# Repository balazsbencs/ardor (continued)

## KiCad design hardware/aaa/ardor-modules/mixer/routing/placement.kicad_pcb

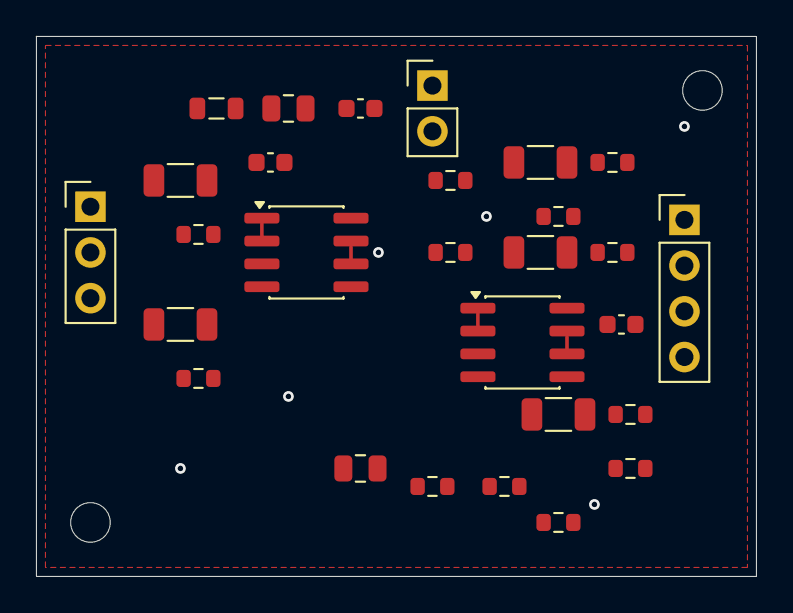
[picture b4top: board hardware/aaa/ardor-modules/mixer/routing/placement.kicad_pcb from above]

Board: 2 copper layers, 40.0 x 30.0 mm, 30 parts (0 on the bottom side), 19 nets.

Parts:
C101: 22u / 25V X5R; C_0805_2012Metric
C102, C404, C405: 100n / 50V X7R; C_0603_1608Metric
C401, C402, C407, C408, C409: 10u / 50V X5R; C_1206_3216Metric
C403: 10u / 25V X5R; C_0805_2012Metric
FB101: BLM21PG601SN1D; L_0805_2012Metric
H1, H2: MountingHole_2.2mm_M2
J101: +5V / GND; PinHeader_1x02_P2.54mm_Vertical
J102: AUDIO_L / GND / AUDIO_R; PinHeader_1x03_P2.54mm_Vertical
J103: OUT_L / GND / OUT_R / OUT_MONO; PinHeader_1x04_P2.54mm_Vertical
R401, R402, R410, R411, R412: 100kR / 1%; R_0603_1608Metric
R403, R404, R405, R406: 10kR / 1%; R_0603_1608Metric
R407, R408, R409: 100R / 1%; R_0603_1608Metric
U401, U402: TLV9002IDR; SOIC-8_3.9x4.9mm_P1.27mm

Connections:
/+5V: FB101.1, J101.1
/+5V_A: C101.1, C102.1, C404.1, C405.1, FB101.2, R405.1, U401.8, U402.8
/GND: C101.2, C102.2, C403.2, C404.2, C405.2, J101.2, J102.2, J103.2, R406.2, R410.2, R411.2, R412.2, U401.4, U402.4
/VREF: R401.2, R402.2, U402.6, U402.7
unnamed: C407.2, R407.1, R410.1
unnamed: C408.2, R408.1, R411.1
unnamed: C409.2, R409.1, R412.1
unnamed: C401.1, J102.1
unnamed: C402.1, J102.3
unnamed: J103.1, R407.2
unnamed: J103.3, R408.2
unnamed: J103.4, R409.2
unnamed: C401.2, R401.1, U401.3
unnamed: C407.1, R403.1, U401.1, U401.2
unnamed: C402.2, R402.1, U401.5
unnamed: C408.1, R404.1, U401.6, U401.7
unnamed: R403.2, R404.2, U402.3
unnamed: C409.1, U402.1, U402.2
unnamed: C403.1, R405.2, R406.1, U402.5

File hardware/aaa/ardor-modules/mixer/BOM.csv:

Reference,Value,Footprint,MPN,JLCPCB Part #,Assembly
J102,STEREO AUDIO INPUT FROM SOURCE,Connector_PinHeader_2.54mm:PinHeader_1x03_P2.54mm_Vertical,PinHeader_1x03_P2.54mm_Vertical,,Manual
J101,5V POWER INPUT,Connector_PinHeader_2.54mm:PinHeader_1x02_P2.54mm_Vertical,PinHeader_1x02_P2.54mm_Vertical,,Manual
J103,"BUFFERED STEREO + MONO AUDIO
OUTPUT",Connector_PinHeader_2.54mm:PinHeader_1x04_P2.54mm_Vertical,PinHeader_1x04_P2.54mm_Vertical,,Manual
FB101,600R@100MHz,Inductor_SMD:L_0805_2012Metric,Murata BLM21PG601SN1D,C41556732,SMT
C101,22u / 25V X5R,Capacitor_SMD:C_0805_2012Metric,Samsung Electro-Mechanics CL21A226MAQNNNE,C45783,SMT
C102,100n / 50V X7R,Capacitor_SMD:C_0603_1608Metric,YAGEO CC0603KRX7R9BB104,C14663,SMT
C401,10u / 50V X5R,Capacitor_SMD:C_1206_3216Metric,Samsung Electro-Mechanics CL31A106KBHNNNE,C13585,SMT
R401,100k / 1%,Resistor_SMD:R_0603_1608Metric,UNI-ROYAL 0603WAF1003T5E,C25803,SMT
U401,TLV9002IDR,Package_SO:SOIC-8_3.9x4.9mm_P1.27mm,Texas Instruments TLV9002IDR,C398360,SMT
R403,10k / 1%,Resistor_SMD:R_0603_1608Metric,UNI-ROYAL 0603WAF1002T5E,C25804,SMT
C402,10u / 50V X5R,Capacitor_SMD:C_1206_3216Metric,Samsung Electro-Mechanics CL31A106KBHNNNE,C13585,SMT
R402,100k / 1%,Resistor_SMD:R_0603_1608Metric,UNI-ROYAL 0603WAF1003T5E,C25803,SMT
R404,10k / 1%,Resistor_SMD:R_0603_1608Metric,UNI-ROYAL 0603WAF1002T5E,C25804,SMT
U402,TLV9002IDR,Package_SO:SOIC-8_3.9x4.9mm_P1.27mm,Texas Instruments TLV9002IDR,C398360,SMT
C407,10u / 50V X5R,Capacitor_SMD:C_1206_3216Metric,Samsung Electro-Mechanics CL31A106KBHNNNE,C13585,SMT
R407,100R / 1%,Resistor_SMD:R_0603_1608Metric,UNI-ROYAL 0603WAF1000T5E,C22775,SMT
R410,100k / 1%,Resistor_SMD:R_0603_1608Metric,UNI-ROYAL 0603WAF1003T5E,C25803,SMT
C408,10u / 50V X5R,Capacitor_SMD:C_1206_3216Metric,Samsung Electro-Mechanics CL31A106KBHNNNE,C13585,SMT
R408,100R / 1%,Resistor_SMD:R_0603_1608Metric,UNI-ROYAL 0603WAF1000T5E,C22775,SMT
R411,100k / 1%,Resistor_SMD:R_0603_1608Metric,UNI-ROYAL 0603WAF1003T5E,C25803,SMT
C409,10u / 50V X5R,Capacitor_SMD:C_1206_3216Metric,Samsung Electro-Mechanics CL31A106KBHNNNE,C13585,SMT
R409,100R / 1%,Resistor_SMD:R_0603_1608Metric,UNI-ROYAL 0603WAF1000T5E,C22775,SMT
R412,100k / 1%,Resistor_SMD:R_0603_1608Metric,UNI-ROYAL 0603WAF1003T5E,C25803,SMT
R405,10k / 1%,Resistor_SMD:R_0603_1608Metric,UNI-ROYAL 0603WAF1002T5E,C25804,SMT
R406,10k / 1%,Resistor_SMD:R_0603_1608Metric,UNI-ROYAL 0603WAF1002T5E,C25804,SMT
C403,10u / 25V X5R,Capacitor_SMD:C_0805_2012Metric,Samsung Electro-Mechanics CL21A106KAYNNNE,C15850,SMT
C404,100n / 50V X7R,Capacitor_SMD:C_0603_1608Metric,YAGEO CC0603KRX7R9BB104,C14663,SMT
C405,100n / 50V X7R,Capacitor_SMD:C_0603_1608Metric,YAGEO CC0603KRX7R9BB104,C14663,SMT

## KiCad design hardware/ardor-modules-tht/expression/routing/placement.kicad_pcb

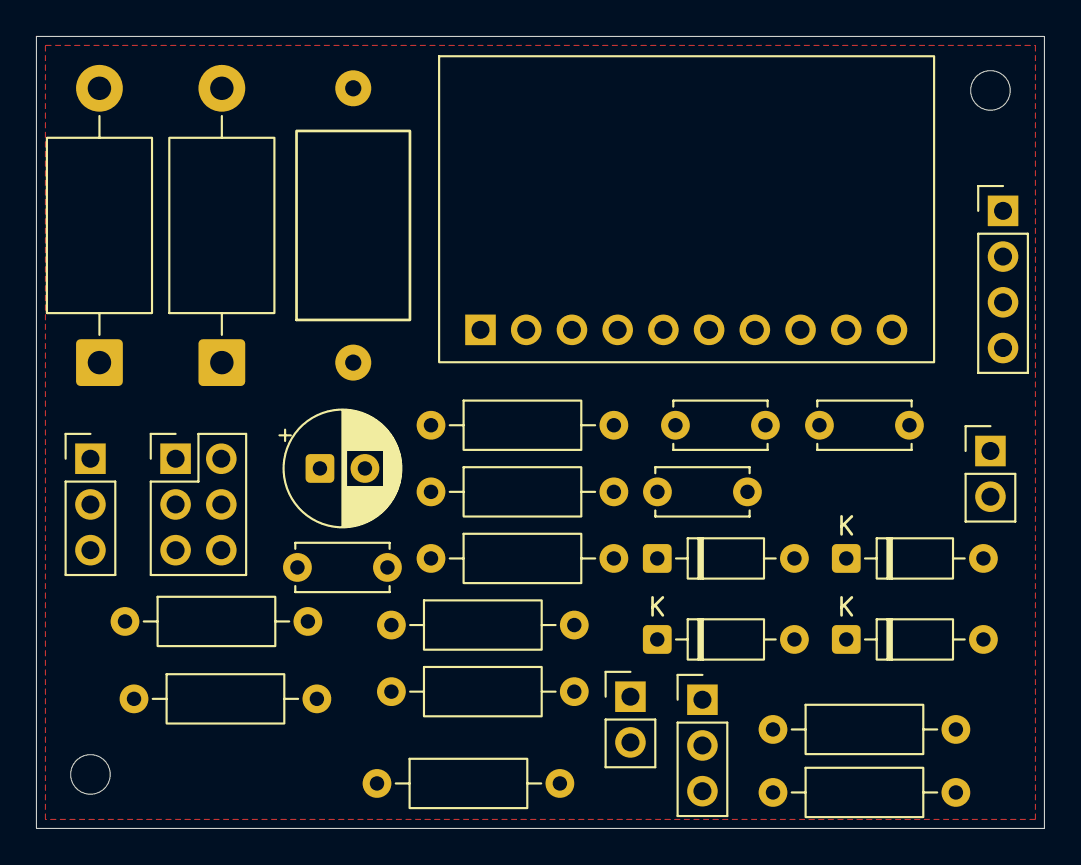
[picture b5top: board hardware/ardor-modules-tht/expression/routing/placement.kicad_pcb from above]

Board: 2 copper layers, 56.0 x 44.0 mm, 31 parts (0 on the bottom side), 17 nets, no tracks yet.

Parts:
C101: 10u / 25V polarized; CP_Radial_D6.3mm_P2.50mm
C102, C301, C302, C303: 100n / 50V X7R; C_Disc_D5.0mm_W2.5mm_P5.00mm
D301, D302: 1.5KE6.8CA; D_TVS_DC_1.5KE_P15.24mm
D303, D304, D305, D306: BAT85S; D_DO-35_SOD27_P7.62mm_Horizontal
FB101: 800R@100MHz / WE 7427501; Ferrite_WE_7427501_P15.24mm
H1, H2: MountingHole_2.2mm_M2
J101: 3V3 POWER INPUT + I2C TO HOST; PinHeader_1x04_P2.54mm_Vertical
J302: PASSIVE PEDAL INPUT / EXCITATION OUTPUT; PinHeader_1x03_P2.54mm_Vertical
JP301: JUMPER ONLY: PEDAL POLARITY; PinHeader_2x03_P2.54mm_Vertical
JP302: JUMPER ONLY: ADC ADDRESS; PinHeader_1x03_P2.54mm_Vertical
JP303: JUMPER ONLY: SDA PULLUP; PinHeader_1x02_P2.54mm_Vertical
JP304: JUMPER ONLY: SCL PULLUP; PinHeader_1x02_P2.54mm_Vertical
R101: 0R / 1% 0.25W; R_Axial_DIN0207_L6.3mm_D2.5mm_P10.16mm_Horizontal
R301: 1kR / 1% 0.25W; R_Axial_DIN0207_L6.3mm_D2.5mm_P10.16mm_Horizontal
R302, R304: 10kR / 1% 0.25W; R_Axial_DIN0207_L6.3mm_D2.5mm_P10.16mm_Horizontal
R303: 1MR / 1% 0.25W; R_Axial_DIN0207_L6.3mm_D2.5mm_P10.16mm_Horizontal
R305, R306: 33R / 1% 0.25W; R_Axial_DIN0207_L6.3mm_D2.5mm_P10.16mm_Horizontal
R307, R308, R309: 2.2kR / 1% 0.25W; R_Axial_DIN0207_L6.3mm_D2.5mm_P10.16mm_Horizontal
U301: ADS1115-M; ADS1115_M_HESTORE_10041798

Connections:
/+3V3: FB101.1, J101.1
/+3V3_A: C101.1, C102.1, C303.1, D303.1, D305.1, FB101.2, JP302.3, R301.1, R307.1, R308.1, R309.1, U301.8
/CHASSIS: D301.2, D302.2, R101.1
/EXP_EXC: JP301.4, R301.2, R304.1
/EXP_RING: D302.1, J302.2, JP301.2, JP301.5
/EXP_TIP: D301.1, J302.1, JP301.1, JP301.6
/GND: C101.2, C102.2, C301.2, C302.2, C303.2, D304.2, D306.2, J101.2, J302.3, JP302.1, R101.2, R303.2, R307.2, U301.3, U301.6, U301.7
/SCL: J101.4, JP304.2, R305.2
/SDA: J101.3, JP303.2, R306.2
unnamed: C301.1, D303.2, D304.1, R302.2, U301.4
unnamed: C302.1, D305.2, D306.1, R304.2, U301.5
unnamed: JP301.3, R302.1, R303.1
unnamed: JP302.2, U301.1
unnamed: JP303.1, R308.2
unnamed: JP304.1, R309.2
unnamed: R305.1, U301.10
unnamed: R306.1, U301.9

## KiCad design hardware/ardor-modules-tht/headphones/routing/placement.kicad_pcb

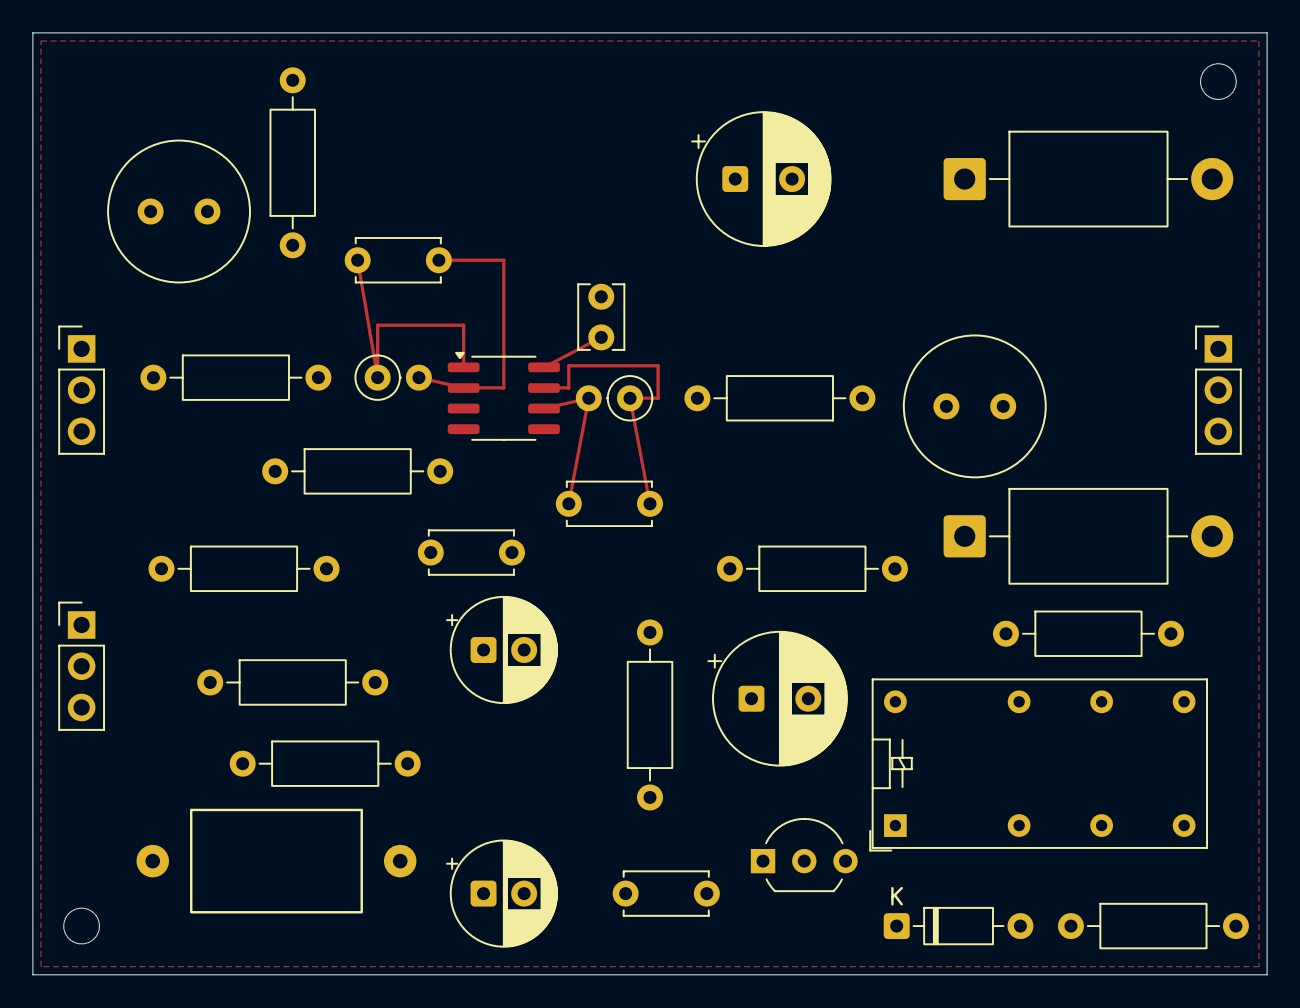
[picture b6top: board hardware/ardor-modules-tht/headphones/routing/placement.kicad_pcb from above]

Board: 2 copper layers, 76.0 x 58.0 mm, 36 parts (0 on the bottom side), 22 nets.

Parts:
C101: 100u / 25V; CP_Radial_D6.3mm_P2.50mm
C102, C632: 100n / 50V X7R; C_Disc_D5.0mm_W2.5mm_P5.00mm
C601, C602: 10u / 50V BIPOLAR; CP_Bipolar_Nichicon_D8.0mm_P3.50mm
C631: 47u / 25V; CP_Radial_D6.3mm_P2.50mm
C641: 100n / 50V X7R / P2.5mm; C_Disc_D3.8mm_W2.6mm_P2.50mm
C651, C652: 470u / 16V; CP_Radial_D8.0mm_P3.50mm
C661, C662: 100p / 50V C0G; C_Disc_D5.0mm_W2.5mm_P5.00mm
D601, D602: 1.5KE6.8CA; D_TVS_DC_1.5KE_P15.24mm
D603: 1N4148; D_DO-35_SOD27_P7.62mm_Horizontal
FB101: 800R@100MHz / WE 7427501; Ferrite_WE_7427501_P15.24mm
H1, H2: MountingHole_2.2mm_M2
J101: 5V POWER + ENABLE INPUT; PinHeader_1x03_P2.54mm_Vertical
J102: STEREO AUDIO INPUT FROM SOURCE; PinHeader_1x03_P2.54mm_Vertical
J602: STEREO HEADPHONE AUDIO OUTPUT; PinHeader_1x03_P2.54mm_Vertical
K601: G5V-2-H1 DC5; Relay_DPDT_Omron_G5V-2
Q601: 2N3904 / E-B-C; TO-92_Inline_Wide
R101: 0R / WIRE LINK; R_Axial_DIN0207_L6.3mm_D2.5mm_P10.16mm_Horizontal
R601: 470R / 1% 0.25W; R_Axial_DIN0207_L6.3mm_D2.5mm_P10.16mm_Horizontal
R602: 100k / 1% 0.25W; R_Axial_DIN0207_L6.3mm_D2.5mm_P10.16mm_Horizontal
R611, R612: 20k / 1% 0.25W; R_Axial_DIN0207_L6.3mm_D2.5mm_P10.16mm_Horizontal
R621, R622: 10k / 1% 0.25W; R_Axial_DIN0207_L6.3mm_D2.5mm_P10.16mm_Horizontal
R631, R632: 10R / 1% 0.25W; R_Axial_DIN0207_L6.3mm_D2.5mm_P10.16mm_Horizontal
R641, R642: 1k / 1% 0.25W; R_Axial_DIN0207_L6.3mm_D2.5mm_P10.16mm_Horizontal
R651, R652: 10k / 1% 0.25W / UPRIGHT; R_Axial_DIN0207_L6.3mm_D2.5mm_P2.54mm_Vertical
U601: OPA1656ID; SOIC-8_3.9x4.9mm_P1.27mm

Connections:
/+5V: D603.1, FB101.1, J101.1, K601.1
/+5V_A: C101.1, C102.1, C641.1, FB101.2, R621.1, U601.8
/CHASSIS: D601.2, D602.2, R101.1
/DRIVE_L: C651.2, K601.8, R641.1
/DRIVE_R: C652.2, K601.9, R642.1
/GND: C101.2, C102.2, C631.2, C632.2, C641.2, J101.2, J102.2, J602.3, K601.6, K601.11, Q601.1, R101.2, R602.2, R622.2, R641.2, R642.2, U601.4
/HP_L: D601.1, J602.1, K601.4
/HP_R: D602.1, J602.2, K601.13
/RELAY_LOW: D603.2, K601.16, Q601.3
/VREF: C631.1, C632.1, R621.2, R622.1, U601.3, U601.5
unnamed: C601.2, R611.1
unnamed: C602.2, R612.1
unnamed: C651.1, R631.2
unnamed: C652.1, R632.2
unnamed: C661.1, R631.1, R651.1, U601.1
unnamed: C662.1, R632.1, R652.1, U601.7
unnamed: J101.3, R601.1
unnamed: C601.1, J102.1
unnamed: C602.1, J102.3
unnamed: Q601.2, R601.2, R602.1
unnamed: C661.2, R611.2, R651.2, U601.2
unnamed: C662.2, R612.2, R652.2, U601.6
